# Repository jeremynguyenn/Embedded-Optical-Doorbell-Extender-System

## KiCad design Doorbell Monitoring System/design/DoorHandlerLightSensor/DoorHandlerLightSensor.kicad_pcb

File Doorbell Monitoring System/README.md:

# DoorHandler
This project presents an electronic doorbell handling and extension system capable of monitoring almost any type of doorbell. The system utilizes a light sensor that periodically checks the door phone to determine whether the signal is active. Upon detection, a transmission pulse is generated and sent to a receiver module, which can be located anywhere within the household. The receiver is designed to provide homeowners with both visual and/or auditory notifications.

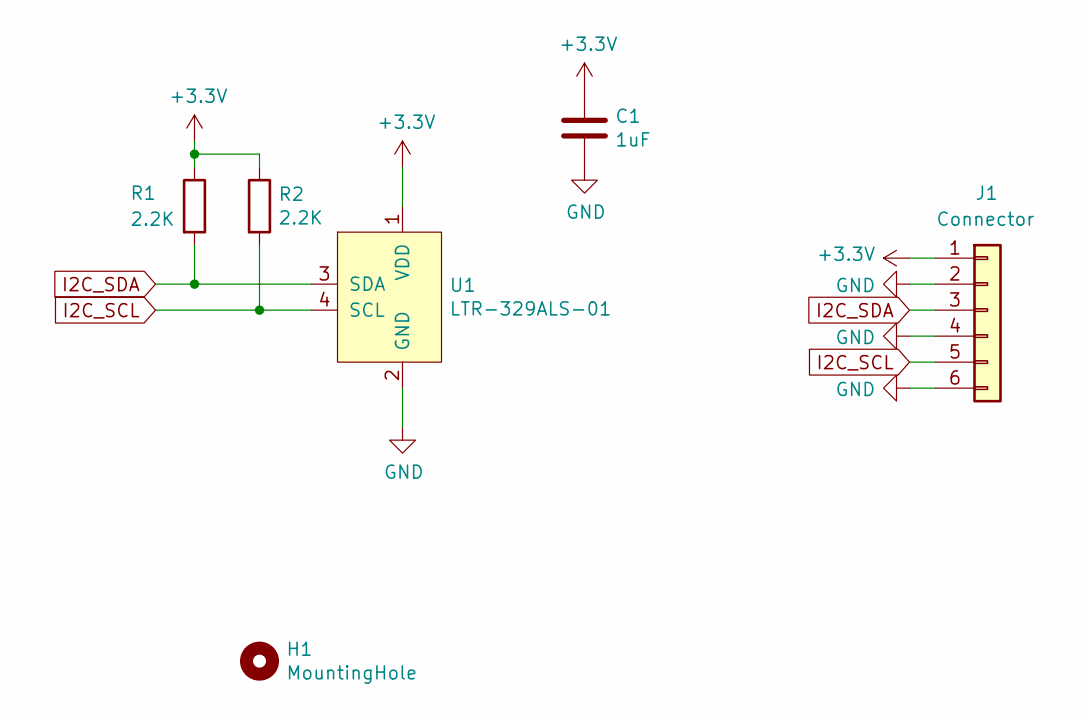
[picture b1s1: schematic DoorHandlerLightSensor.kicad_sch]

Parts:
C1: 1uF; C_0805_2012Metric
H1: MountingHole; MountingHole_3.2mm_M3_Pad_Via
J1: Connector; AFA07-S06FCA-00
R1, R2: 2.2K; R_1206_3216Metric
U1: LTR-329ALS-01

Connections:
+3V3: C1.1, J1.1, R1.1, R2.1, U1.1 (VDD)
GND: C1.2, J1.2, J1.4, J1.6, U1.2 (GND)
I2C_SCL: J1.5, R2.2, U1.4 (SCL)
I2C_SDA: J1.3, R1.2, U1.3 (SDA)

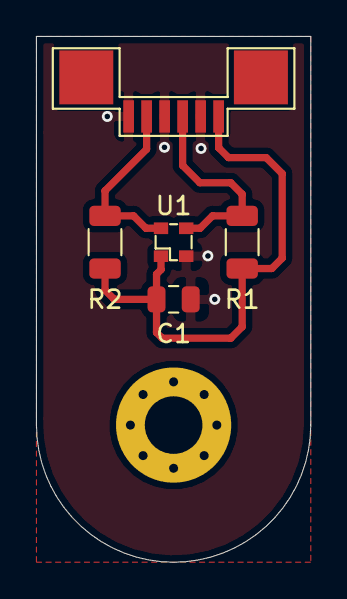
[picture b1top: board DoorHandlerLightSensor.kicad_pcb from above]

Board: 2 copper layers, 15.2 x 29.2 mm, 6 parts (0 on the bottom side), 4 nets.

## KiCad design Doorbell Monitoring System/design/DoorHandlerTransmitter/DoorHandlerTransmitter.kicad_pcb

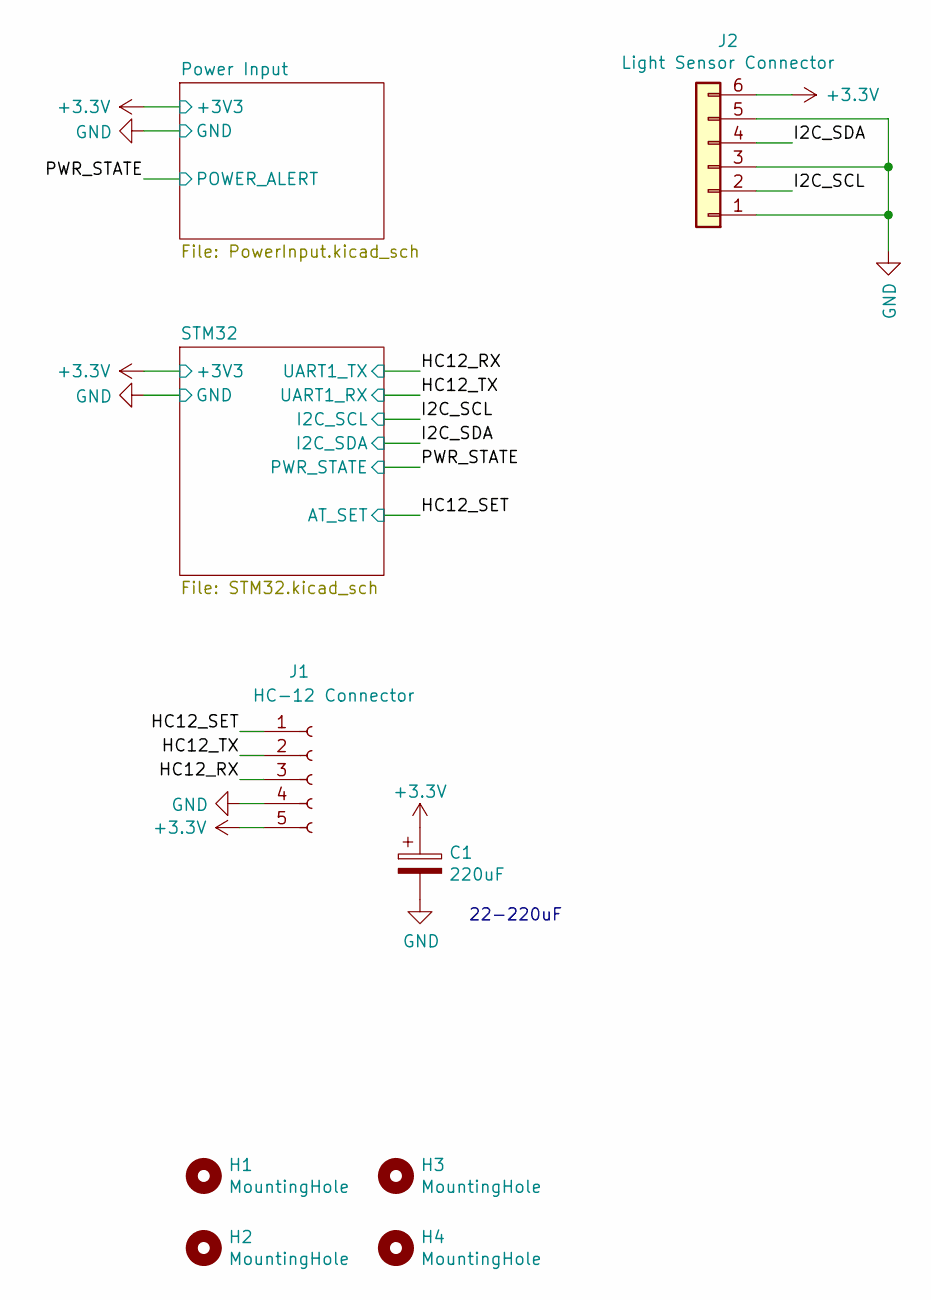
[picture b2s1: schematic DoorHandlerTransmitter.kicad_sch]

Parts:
C1: 220uF; CP_Elec_8x10.5
H1, H2, H3, H4: MountingHole; MountingHole_3mm_Pad_Via
J1: HC-12 Connector; PinSocket_1x05_P2.54mm_Vertical
J2: Light Sensor Connector; AFA07-S06FCA-00

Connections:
+3V3: C1.1, J1.5, J2.6; also elsewhere on the board
/HC12_RX: J1.3; also elsewhere on the board
/HC12_SET: J1.1; also elsewhere on the board
/HC12_TX: J1.2; also elsewhere on the board
/I2C_SCL: J2.2; also elsewhere on the board
/I2C_SDA: J2.4; also elsewhere on the board
GND: C1.2, J1.4, J2.1, J2.3, J2.5; also elsewhere on the board

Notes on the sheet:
22-220uF

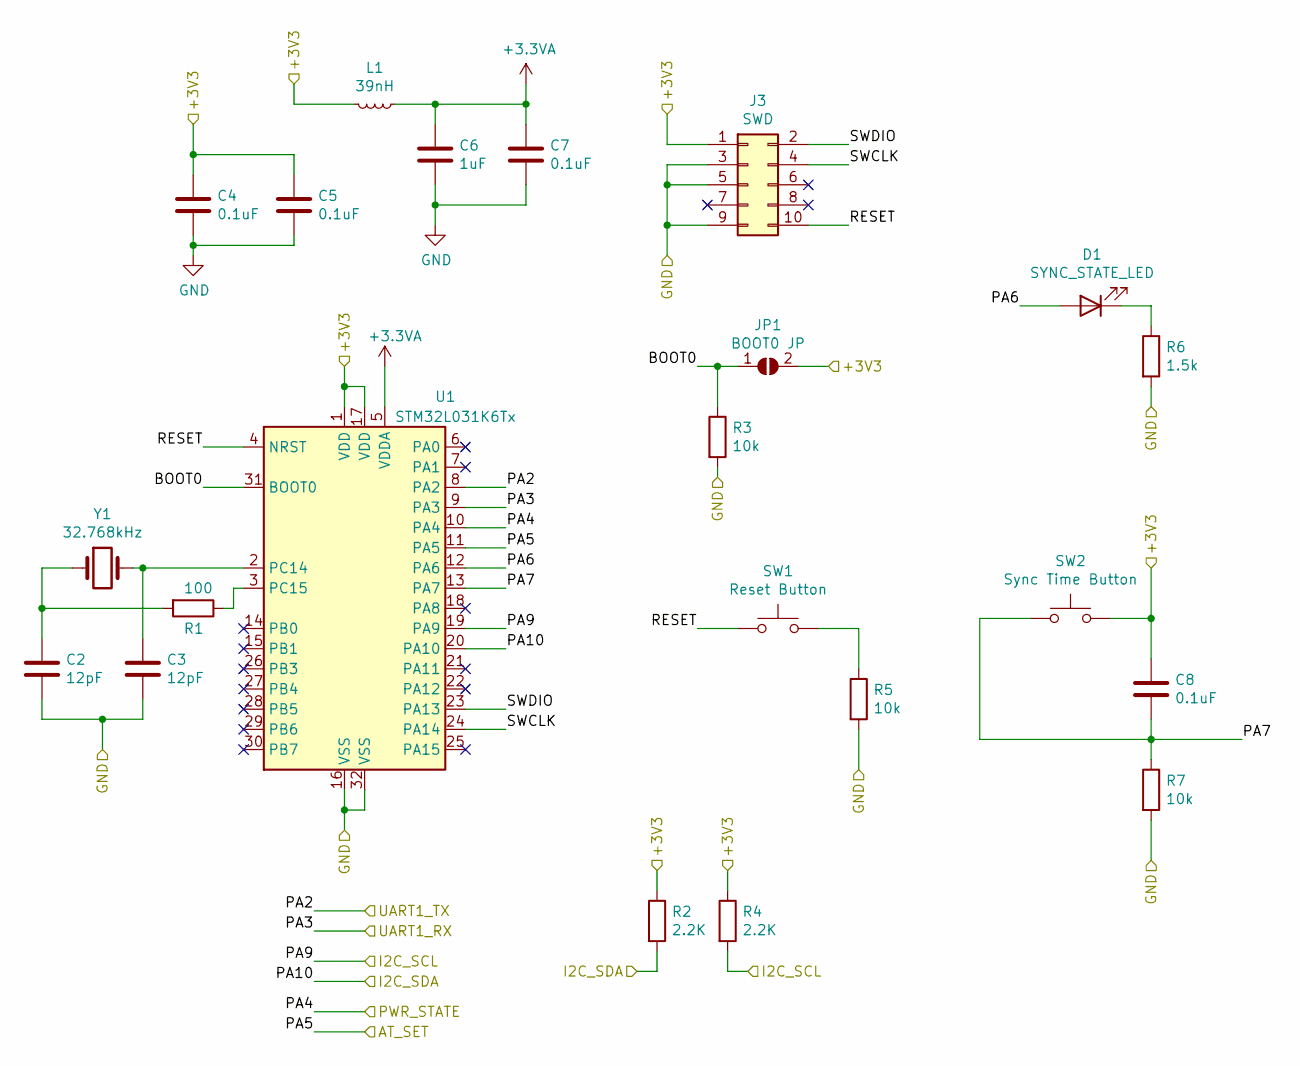
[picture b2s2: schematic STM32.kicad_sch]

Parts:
C2, C3: 12pF; C_0805_2012Metric
C4, C5, C7, C8: 0.1uF; C_0805_2012Metric
C6: 1uF; C_0805_2012Metric
D1: SYNC_STATE_LED; LED_0603_1608Metric
J3: SWD; PinHeader_2x05_P2.54mm_Vertical
JP1: BOOT0 JP; SolderJumper-2_P1.3mm_Open_RoundedPad1.0x1.5mm
L1: 39nH; L_0805_2012Metric_Pad1.15x1.40mm_HandSolder
R1: 100; R_1206_3216Metric
R2, R4: 2.2K; R_1206_3216Metric
R3, R5, R7: 10k; R_1206_3216Metric
R6: 1.5k; R_1206_3216Metric
SW1: Reset Button; SW_SPST_TL3342
SW2: Sync Time Button; SW_SPST_TL3342
U1: STM32L031K6Tx; LQFP-32_7x7mm_P0.8mm
Y1: 32.768kHz; Crystal_Round_D1.5mm_Vertical

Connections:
+3.3VA: C6.1, C7.1, L1.1, U1.5 (VDDA)
+3V3: C4.1, C5.1, C8.1, J3.1, JP1.2 (B), L1.2, R2.1, R4.1, SW2.2, U1.1 (VDD), U1.17 (VDD); also elsewhere on the board
/HC12_RX: U1.8 (PA2); also elsewhere on the board
/HC12_SET: U1.11 (PA5); also elsewhere on the board
/HC12_TX: U1.9 (PA3); also elsewhere on the board
/I2C_SCL: R4.2, U1.19 (PA9); also elsewhere on the board
/I2C_SDA: R2.2, U1.20 (PA10); also elsewhere on the board
/PWR_STATE: U1.10 (PA4); also elsewhere on the board
/STM32/BOOT0: JP1.1 (A), R3.1, U1.31 (BOOT0)
/STM32/PA6: D1.2 (A), U1.12 (PA6)
/STM32/PA7: C8.2, R7.1, SW2.1, U1.13 (PA7)
/STM32/RESET: J3.10, SW1.1, U1.4 (NRST)
/STM32/SWCLK: J3.4, U1.24 (PA14)
/STM32/SWDIO: J3.2, U1.23 (PA13)
GND: C2.2, C3.2, C4.2, C5.2, C6.2, C7.2, J3.3, J3.5, J3.9, R3.2, R5.2, R6.2, R7.2, U1.16 (VSS), U1.32 (VSS); also elsewhere on the board
unnamed: C2.1, R1.2, Y1.1
unnamed: C3.1, U1.2 (PC14), Y1.2
unnamed: D1.1 (K), R6.1
unnamed: R1.1, U1.3 (PC15)
unnamed: R5.1, SW1.2

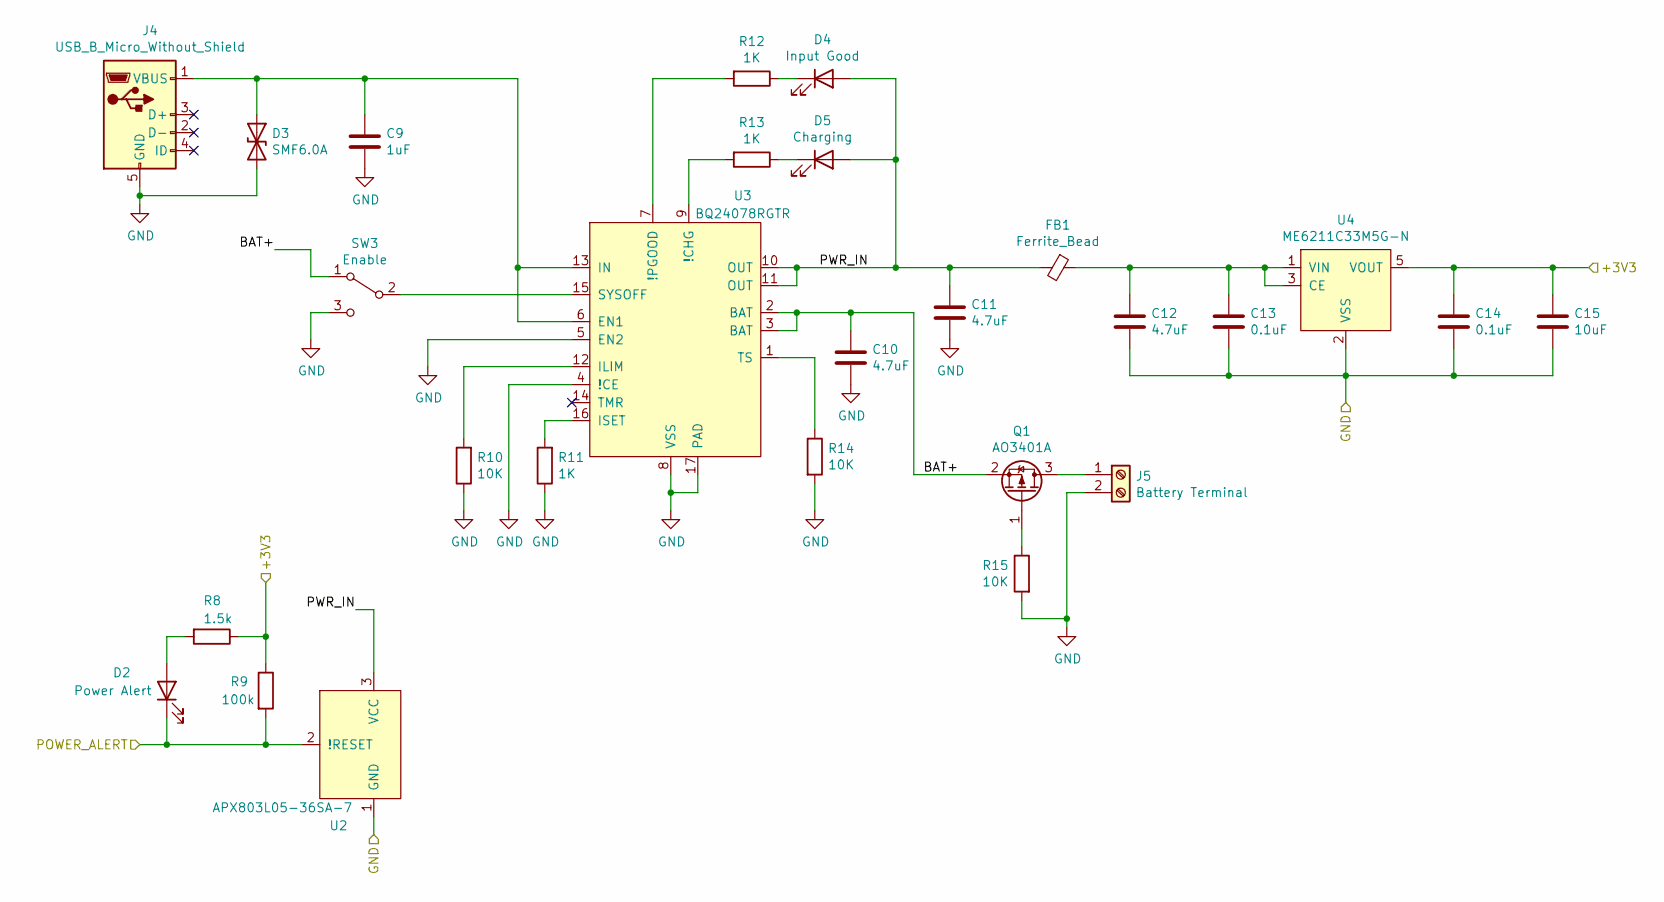
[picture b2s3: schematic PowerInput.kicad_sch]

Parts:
C9: 1uF; C_0805_2012Metric
C10, C11, C12: 4.7uF; C_0805_2012Metric
C13, C14: 0.1uF; C_0805_2012Metric
C15: 10uF; C_1206_3216Metric
D2: Power Alert; LED_0603_1608Metric
D3: SMF6.0A; D_SOD-123F
D4: Input Good; LED_0603_1608Metric
D5: Charging; LED_0603_1608Metric
FB1: Ferrite_Bead; L_0805_2012Metric_Pad1.15x1.40mm_HandSolder
J4: USB_B_Micro_Without_Shield; Micro_USB_B_Female
J5: Battery Terminal; Hirose_DF13-02P-1.25DSA_1x02_P1.25mm_Vertical
Q1: AO3401A; SOT-23
R8: 1.5k; R_1206_3216Metric
R9: 100k; R_1206_3216Metric
R10, R14, R15: 10K; R_1206_3216Metric
R11, R12, R13: 1K; R_1206_3216Metric
SW3: Enable; Toggle-Switch-SK12D07VG4
U2: APX803L05-36SA-7; SOT-23W_Handsoldering
U3: BQ24078RGTR; VQFN-16-1EP_3x3mm_P0.5mm_EP1.45x1.45mm
U4: ME6211C33M5G-N; SOT-23-5

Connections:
+3V3: C14.1, C15.1, R8.1, R9.1, U4.5 (VOUT); also elsewhere on the board
/PWR_STATE: D2.1 (K), R9.2, U2.2 (!RESET); also elsewhere on the board
/Power Input/BAT+: C10.1, Q1.2 (S), SW3.1 (A), U3.2 (BAT), U3.3 (BAT)
/Power Input/PWR_IN: C11.1, D4.2 (A), D5.2 (A), FB1.2, U2.3 (VCC), U3.10 (OUT), U3.11 (OUT)
GND: C9.2, C10.2, C11.2, C12.2, C13.2, C14.2, C15.2, D3.2 (A2), J4.5 (GND), J5.2, R10.1, R11.1, R14.2, R15.2, SW3.3 (C), U2.1 (GND), U3.4 (!CE), U3.5 (EN2), U3.8 (VSS), U3.17 (PAD), U4.2 (VSS); also elsewhere on the board
unnamed: C9.1, D3.1 (A1), J4.1 (VBUS), U3.6 (EN1), U3.13 (IN)
unnamed: C12.1, C13.1, FB1.1, U4.1 (VIN), U4.3 (CE)
unnamed: D2.2 (A), R8.2
unnamed: D4.1 (K), R12.1
unnamed: D5.1 (K), R13.1
unnamed: J5.1, Q1.3 (D)
unnamed: Q1.1 (G), R15.1
unnamed: R10.2, U3.12 (ILIM)
unnamed: R11.2, U3.16 (ISET)
unnamed: R12.2, U3.7 (!PGOOD)
unnamed: R13.2, U3.9 (!CHG)
unnamed: R14.1, U3.1 (TS)
unnamed: SW3.2 (B), U3.15 (SYSOFF)

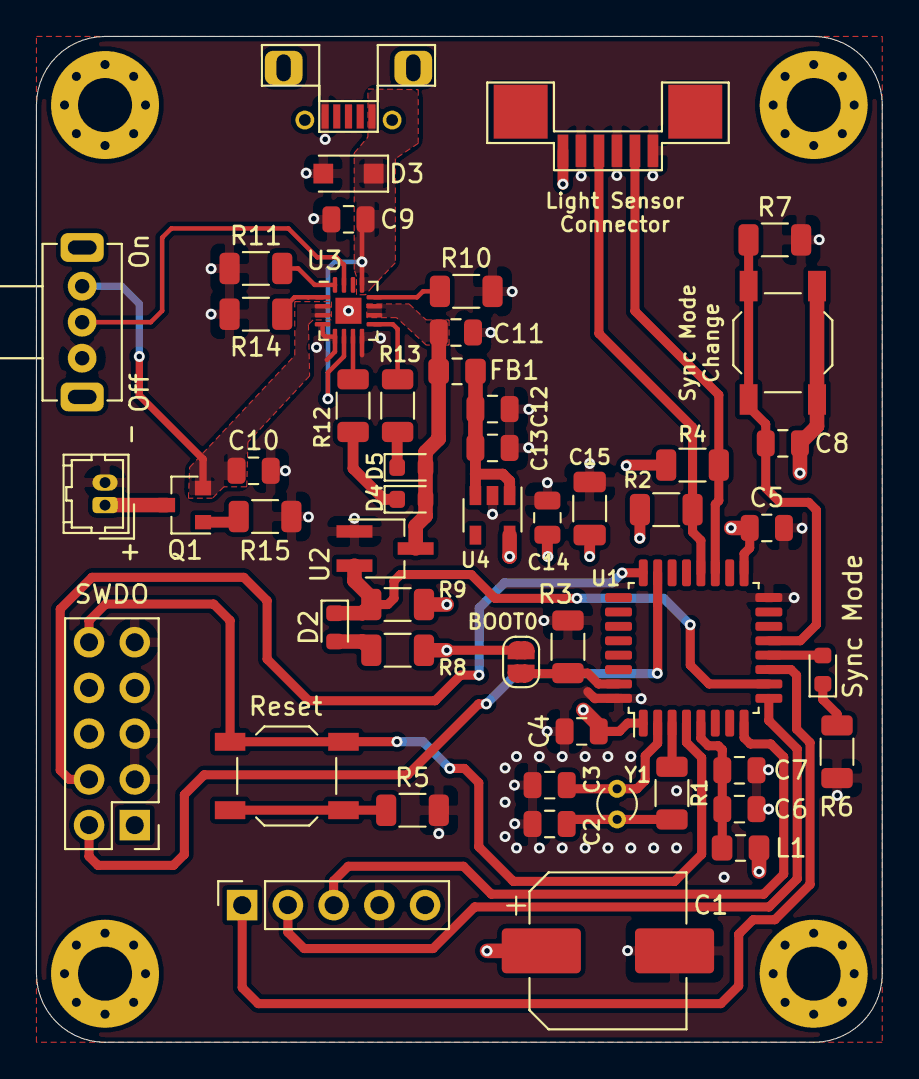
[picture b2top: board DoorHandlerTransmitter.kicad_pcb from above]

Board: 4 copper layers, 47.0 x 55.9 mm, 56 parts (0 on the bottom side), 35 nets.

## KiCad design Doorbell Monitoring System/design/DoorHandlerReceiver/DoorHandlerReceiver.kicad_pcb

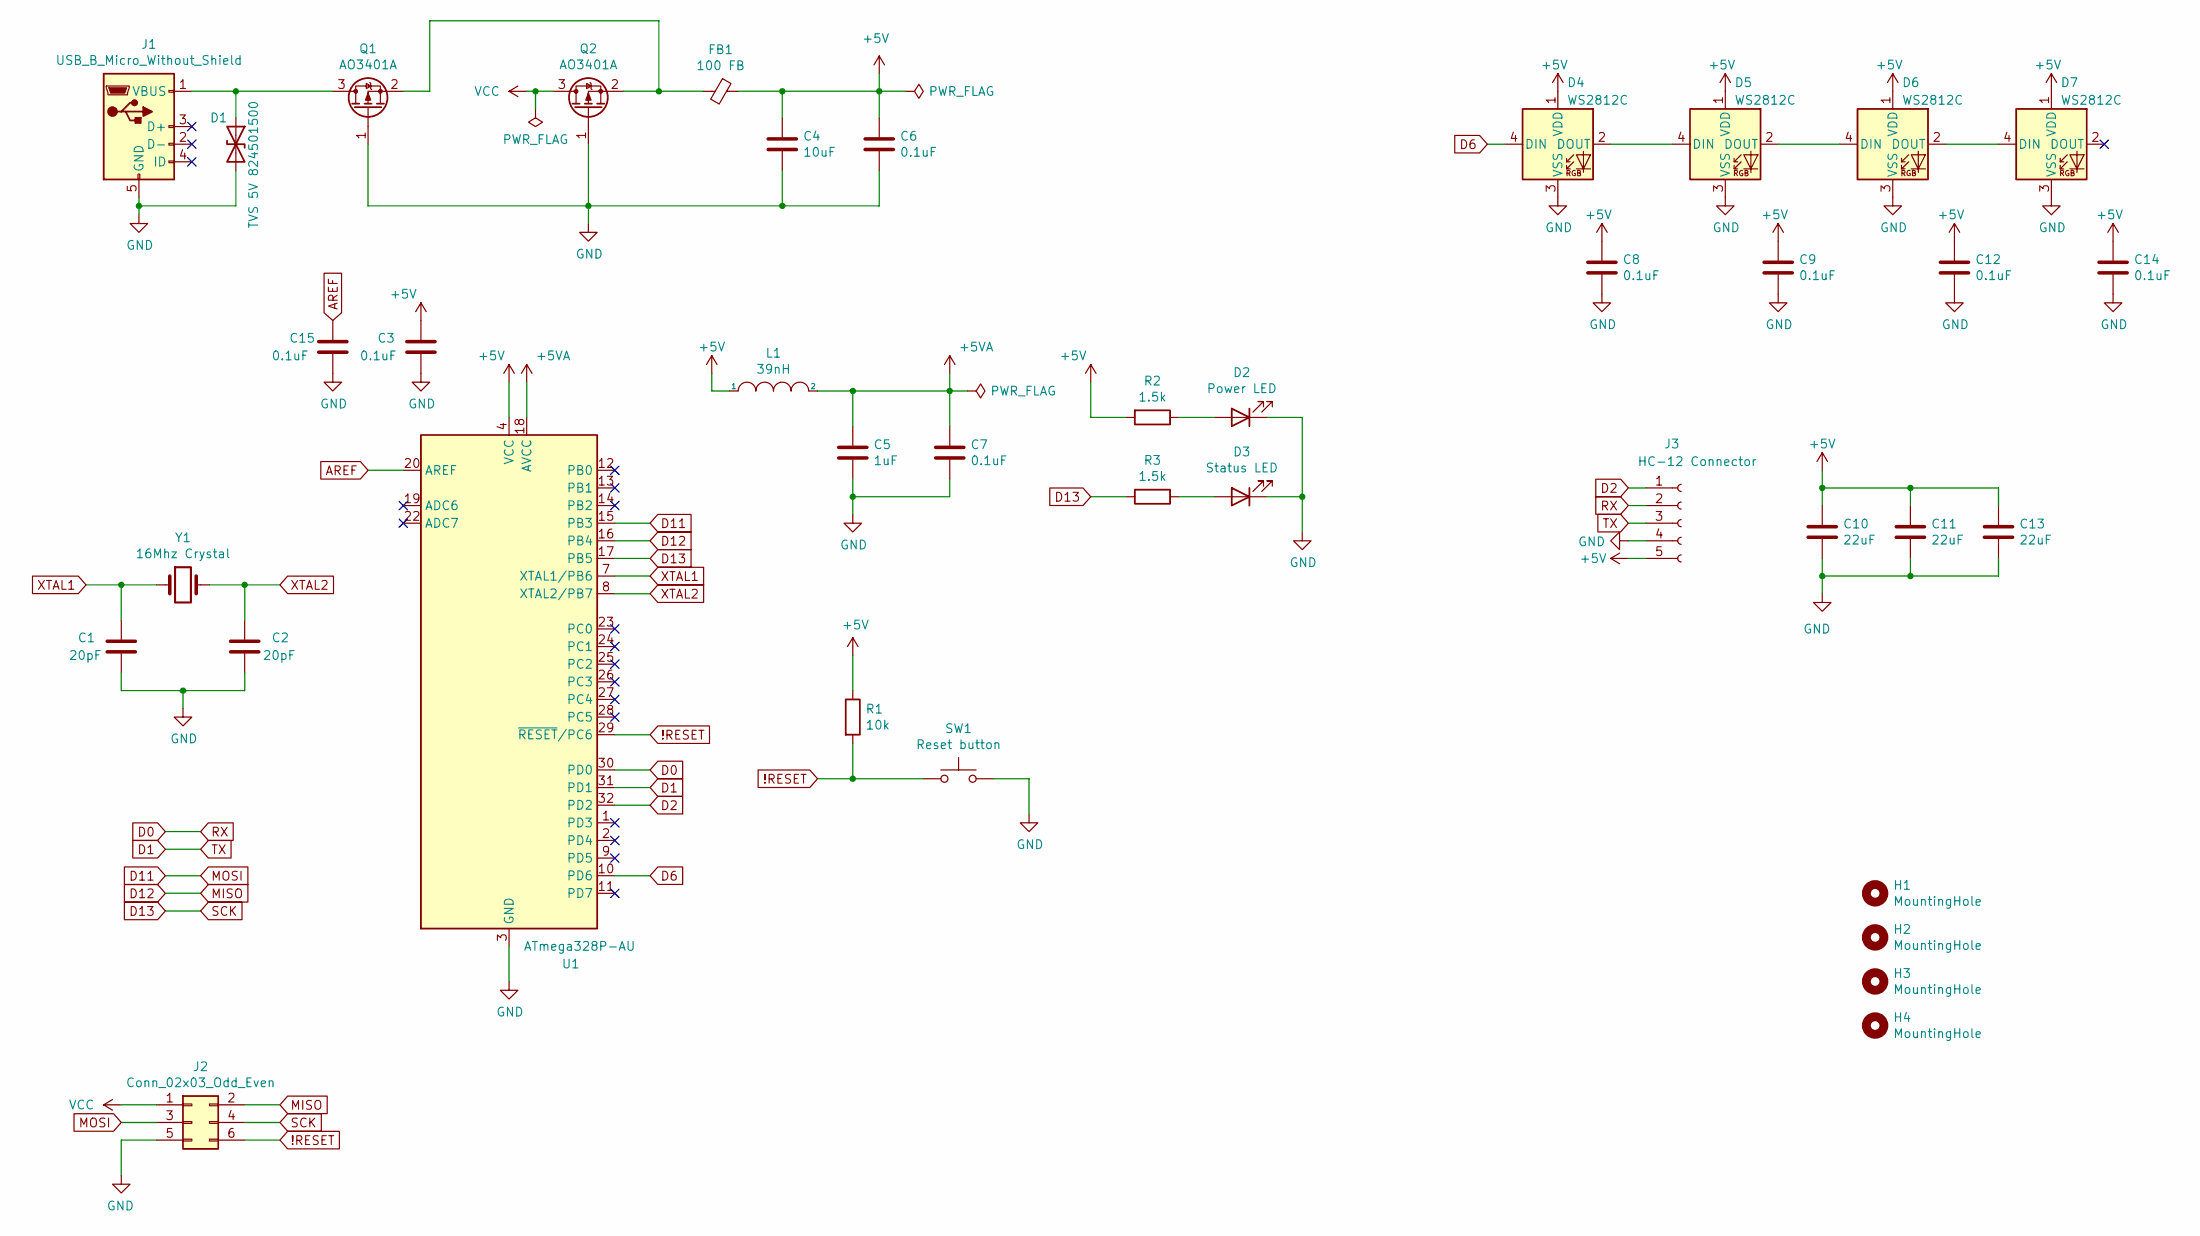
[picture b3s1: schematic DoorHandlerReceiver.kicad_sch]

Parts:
C1, C2: 20pF; C_0805_2012Metric
C3, C6, C7, C8, C9, C12, C14, C15: 0.1uF; C_0805_2012Metric
C4: 10uF; C_1206_3216Metric
C5: 1uF; C_0805_2012Metric
C10, C11, C13: 22uF; C_0805_2012Metric
D1: TVS 5V 824501500; D_SMA
D2: Power LED; LED_0603_1608Metric
D3: Status LED; LED_0603_1608Metric
D4, D5, D6, D7: WS2812C; LED_WS2812B_PLCC4_5.0x5.0mm_P3.2mm
FB1: 100 FB; L_0805_2012Metric_Pad1.05x1.20mm_HandSolder
H1, H2, H3, H4: MountingHole; MountingHole_3.2mm_M3_Pad_Via
J1: USB_B_Micro_Without_Shield; Micro_USB_B_Female
J2: Conn_02x03_Odd_Even; PinSocket_2x03_P2.54mm_Vertical
J3: HC-12 Connector; PinSocket_1x05_P2.54mm_Vertical
L1: 39nH; L_0805_2012Metric_Pad1.15x1.40mm_HandSolder
Q1, Q2: AO3401A; SOT-23
R1: 10k; R_1206_3216Metric
R2, R3: 1.5k; R_1206_3216Metric
SW1: Reset button; SW_SPST_TL3342
U1: ATmega328P-AU; TQFP-32_7x7mm_P0.8mm
Y1: 16Mhz Crystal; Crystal_HC49-U_Vertical

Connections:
!RESET: J2.6, R1.2, SW1.1, U1.29 (~RESET/PC6)
+5V: C3.1, C4.1, C6.1, C8.1, C9.1, C10.1, C11.1, C12.1, C13.1, C14.1, D4.1 (VDD), D5.1 (VDD), D6.1 (VDD), D7.1 (VDD), FB1.1, J3.5, L1.1, R1.1, R2.2, U1.4 (VCC), U1.6 (VCC)
+5VA: C5.1, C7.1, L1.2, U1.18 (AVCC)
AREF: C15.1, U1.20 (AREF)
D0: J3.2, U1.30 (PD0)
D1: J3.3, U1.31 (PD1)
D2: J3.1, U1.32 (PD2)
D6: D4.4 (DIN), U1.10 (PD6)
D11: J2.3, U1.15 (PB3)
D12: J2.2, U1.16 (PB4)
D13: J2.4, R3.2, U1.17 (PB5)
GND: C1.2, C2.2, C3.2, C4.2, C5.2, C6.2, C7.2, C8.2, C9.2, C10.2, C11.2, C12.2, C13.2, C14.2, C15.2, D1.2 (A2), D2.1 (K), D3.1 (K), D4.3 (VSS), D5.3 (VSS), D6.3 (VSS), D7.3 (VSS), J1.5 (GND), J2.5, J3.4, Q1.1 (G), Q2.1 (G), SW1.2, U1.3 (GND), U1.5 (GND), U1.21 (GND)
unnamed: D1.1 (A1), J1.1 (VBUS), Q1.3 (D)
unnamed: D2.2 (A), R2.1
unnamed: D3.2 (A), R3.1
unnamed: D4.2 (DOUT), D5.4 (DIN)
unnamed: D5.2 (DOUT), D6.4 (DIN)
unnamed: D6.2 (DOUT), D7.4 (DIN)
unnamed: FB1.2, Q1.2 (S), Q2.2 (S)
VCC: J2.1, Q2.3 (D)
XTAL1: C1.1, U1.7 (XTAL1/PB6), Y1.1
XTAL2: C2.1, U1.8 (XTAL2/PB7), Y1.2

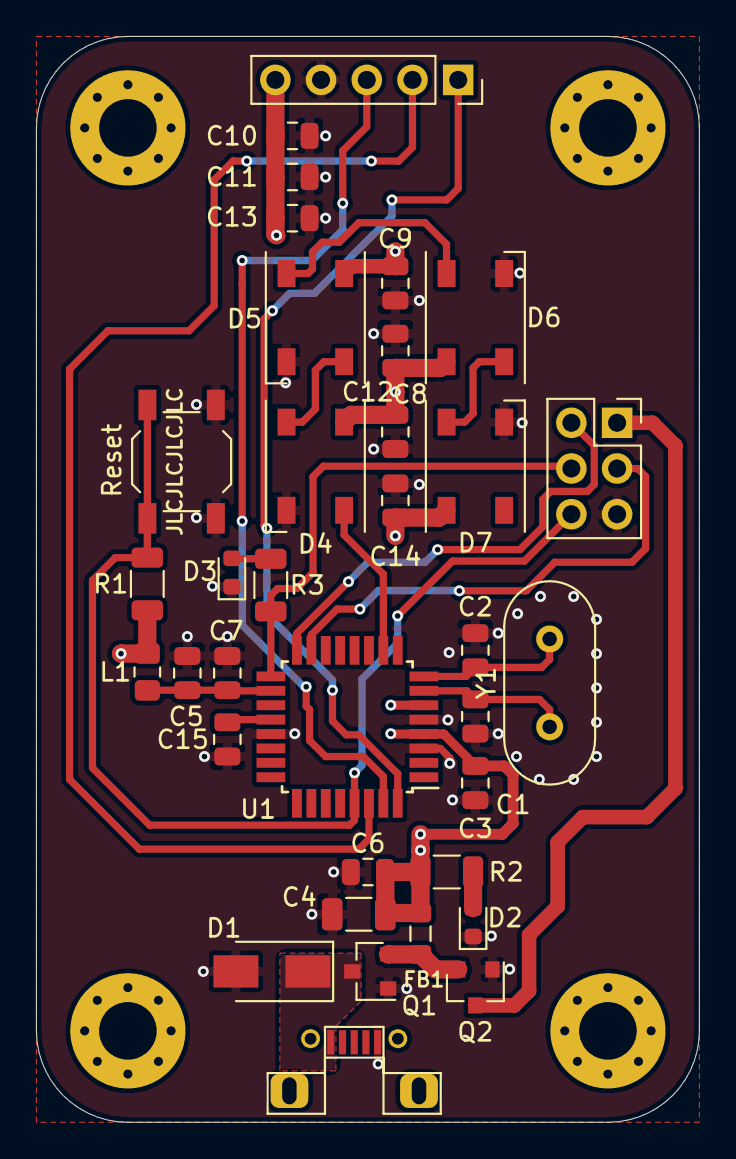
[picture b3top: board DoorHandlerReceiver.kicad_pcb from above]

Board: 4 copper layers, 36.8 x 60.3 mm, 39 parts (0 on the bottom side), 22 nets.

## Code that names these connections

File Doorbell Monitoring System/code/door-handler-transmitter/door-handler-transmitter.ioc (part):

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Mcu.Name=STM32L031K(4-6)Ux
Mcu.Package=UFQFPN32
Mcu.UserName=STM32L031K6Ux
PA10.Mode=I2C
PA10.Signal=I2C1_SDA
PA2.Mode=Asynchronous
PA2.Signal=LPUART1_TX
PA3.Mode=Asynchronous
PA3.Signal=LPUART1_RX
PA5.GPIOParameters=PinState,GPIO_Label
PA5.GPIO_Label=AT_SET
PA5.PinState=GPIO_PIN_SET
PA5.Signal=GPIO_Output
PA6.GPIOParameters=PinState,GPIO_Label
PA6.GPIO_Label=SYNC_STATE_LED
PA6.PinState=GPIO_PIN_RESET
PA6.Signal=GPIO_Output
PA7.GPIOParameters=GPIO_Label
PA7.GPIO_Label=SYNC_TIME_BTN
PA7.Signal=GPXTI7
PA9.Mode=I2C
PA9.Signal=I2C1_SCL
PC14-OSC32_IN.Mode=LSE-External-Oscillator
PC14-OSC32_IN.Signal=RCC_OSC32_IN
PC15-OSC32_OUT.Mode=LSE-External-Oscillator
PC15-OSC32_OUT.Signal=RCC_OSC32_OUT
RCC.HSE_VALUE=8000000
RCC.SYSCLKFreq_VALUE=16000000
RCC.SYSCLKSource=RCC_SYSCLKSOURCE_HSI
board=custom

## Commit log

2025-09-02 finalversion
2025-09-02 Create LICENSE
